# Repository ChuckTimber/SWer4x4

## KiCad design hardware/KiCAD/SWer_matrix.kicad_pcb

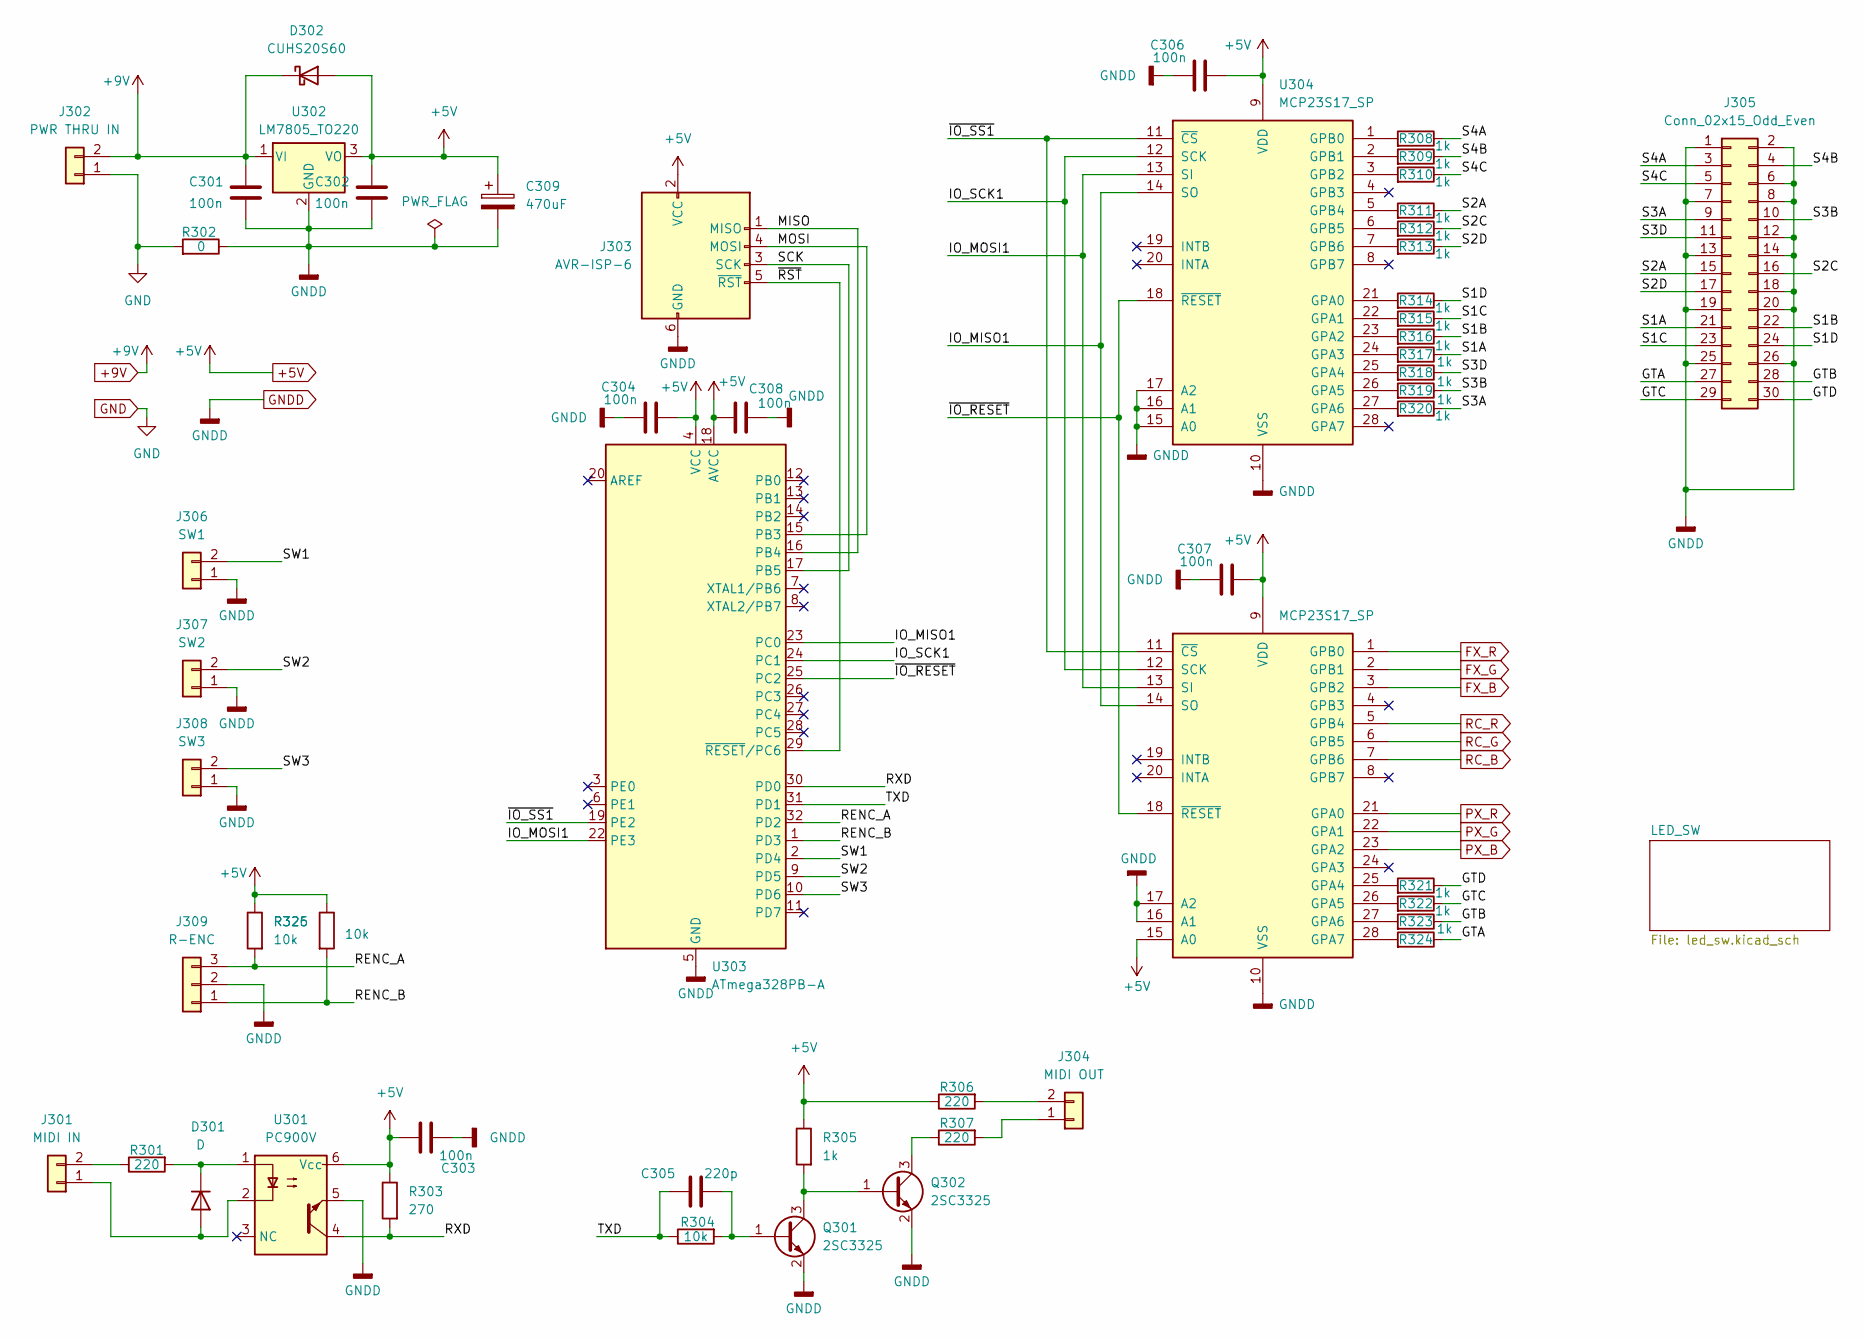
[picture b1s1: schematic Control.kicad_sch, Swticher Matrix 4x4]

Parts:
C301, C302, C303, C304, C306, C307, C308: 100n; C_0603_1608Metric_Pad1.08x0.95mm_HandSolder
C305: 220p; C_Disc_D6.0mm_W2.5mm_P5.00mm
C309: 470uF; CP_Radial_D12.5mm_P5.00mm
D301: D; Nexperia_CFP3_SOD-123W
D302: CUHS20S60; D_1210_3225Metric_Pad1.42x2.65mm_HandSolder
J301: MIDI IN; PinSocket_1x02_P2.54mm_Vertical
J302: PWR THRU IN; PinSocket_1x02_P2.54mm_Vertical
J303: AVR-ISP-6; PinHeader_2x03_P2.54mm_Vertical
J304: MIDI OUT; PinSocket_1x02_P2.54mm_Vertical
J305: Conn_02x15_Odd_Even; PinHeader_2x15_P2.54mm_Vertical
J306: SW1; PinSocket_1x02_P2.54mm_Vertical
J307: SW2; PinSocket_1x02_P2.54mm_Vertical
J308: SW3; PinSocket_1x02_P2.54mm_Vertical
J309: R-ENC; PinHeader_1x03_P2.54mm_Vertical
Q301, Q302: 2SC3325; SOT-323_SC-70
R301, R306, R307: 220; R_0603_1608Metric_Pad0.98x0.95mm_HandSolder
R302: 0; R_0603_1608Metric_Pad0.98x0.95mm_HandSolder
R303: 270; R_Axial_DIN0204_L3.6mm_D1.6mm_P2.54mm_Vertical
R304, R325, R326: 10k; R_0603_1608Metric_Pad0.98x0.95mm_HandSolder
R305, R308, R309, R310, R311, R312, R313, R314, R315, R316, R317, R318, R319, R320, R321, R322, R323, R324: 1k; R_0603_1608Metric_Pad0.98x0.95mm_HandSolder
U301: PC900V; DIP-6_W7.62mm
U302: LM7805_TO220; TO-220-3_Vertical
U303: ATmega328PB-A; TQFP-32_7x7mm_P0.8mm
U304, U305: MCP23S17_SP; DIP-28_W7.62mm

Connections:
+5V: C302.1, C303.2, C304.2, C306.2, C307.2, C308.2, C309.1, D302.2 (A), J303.2 (VCC), R303.1, R305.1, R306.1, R325.1, R326.1, U301.6 (Vcc), U302.3 (VO), U303.4 (VCC), U303.18 (AVCC), U304.9 (VDD), U305.9 (VDD), U305.15 (A0); also elsewhere on the board
+9V: C301.1, D302.1 (K), J302.2, U302.1 (VI); also elsewhere on the board
/Control/GTA: J305.27, R324.1
/Control/GTB: J305.28, R323.1
/Control/GTC: J305.29, R322.1
/Control/GTD: J305.30, R321.1
/Control/IO_MISO1: U303.23 (PC0), U304.14 (SO), U305.14 (SO)
/Control/IO_MOSI1: U303.22 (PE3), U304.13 (SI), U305.13 (SI)
/Control/IO_SCK1: U303.24 (PC1), U304.12 (SCK), U305.12 (SCK)
/Control/MISO: J303.1 (MISO), U303.16 (PB4)
/Control/MOSI: J303.4 (MOSI), U303.15 (PB3)
/Control/RENC_A: J309.3, R325.2, U303.32 (PD2)
/Control/RENC_B: J309.1, R326.2, U303.1 (PD3)
/Control/RXD: R303.2, U301.4, U303.30 (PD0)
/Control/S1A: J305.21, R317.1
/Control/S1B: J305.22, R316.1
/Control/S1C: J305.23, R315.1
/Control/S1D: J305.24, R314.1
/Control/S2A: J305.15, R311.1
/Control/S2C: J305.16, R312.1
/Control/S2D: J305.17, R313.1
/Control/S3A: J305.9, R320.1
/Control/S3B: J305.10, R319.1
/Control/S3D: J305.11, R318.1
/Control/S4A: J305.3, R308.1
/Control/S4B: J305.4, R309.1
/Control/S4C: J305.5, R310.1
/Control/SCK: J303.3 (SCK), U303.17 (PB5)
/Control/SW1: J306.2, U303.2 (PD4)
/Control/SW2: J307.2, U303.9 (PD5)
/Control/SW3: J308.2, U303.10 (PD6)
/Control/TXD: C305.1, R304.1, U303.31 (PD1)
/Control/~IO_RESET: U303.25 (PC2), U304.18 (~RESET), U305.18 (~RESET)
/Control/~IO_SS1: U303.19 (PE2), U304.11 (~CS), U305.11 (~CS)
/Control/~RST: J303.5 (~RST), U303.29 (~RESET/PC6)
FX_B: U305.3 (GPB2); also elsewhere on the board
FX_G: U305.2 (GPB1); also elsewhere on the board
FX_R: U305.1 (GPB0); also elsewhere on the board
GND: J302.1, R302.2; also elsewhere on the board
GNDD: C301.2, C302.2, C303.1, C304.1, C306.1, C307.1, C308.1, C309.2, J303.6 (GND), J305.1, J305.2, J305.6, J305.7, J305.8, J305.12, J305.13, J305.14, J305.18, J305.19, J305.20, J305.25, J305.26, J306.1, J307.1, J308.1, J309.2, Q301.2 (E), Q302.2 (E), R302.1, U301.5, U302.2 (GND), U303.5 (GND), U303.21 (GND), U304.10 (VSS), U304.15 (A0), U304.16 (A1), U304.17 (A2), U305.10 (VSS), U305.16 (A1), U305.17 (A2); also elsewhere on the board
unnamed: D301.2 (A), J301.1, U301.2
unnamed: D301.1 (K), R301.2, U301.1
unnamed: J301.2, R301.1
unnamed: J304.1, R307.2
unnamed: J304.2, R306.2
unnamed: C305.2, Q301.1 (B), R304.2
unnamed: Q301.3 (C), Q302.1 (B), R305.2
unnamed: Q302.3 (C), R307.1
unnamed: R314.2, U304.21 (GPA0)
unnamed: R315.2, U304.22 (GPA1)
unnamed: R316.2, U304.23 (GPA2)
unnamed: R317.2, U304.24 (GPA3)
unnamed: R318.2, U304.25 (GPA4)
unnamed: R319.2, U304.26 (GPA5)
unnamed: R320.2, U304.27 (GPA6)
unnamed: R308.2, U304.1 (GPB0)
unnamed: R309.2, U304.2 (GPB1)
unnamed: R310.2, U304.3 (GPB2)
unnamed: R311.2, U304.5 (GPB4)
unnamed: R312.2, U304.6 (GPB5)
unnamed: R313.2, U304.7 (GPB6)
unnamed: R321.2, U305.25 (GPA4)
unnamed: R322.2, U305.26 (GPA5)
unnamed: R323.2, U305.27 (GPA6)
unnamed: R324.2, U305.28 (GPA7)
PX_B: U305.23 (GPA2); also elsewhere on the board
PX_G: U305.22 (GPA1); also elsewhere on the board
PX_R: U305.21 (GPA0); also elsewhere on the board
RC_B: U305.7 (GPB6); also elsewhere on the board
RC_G: U305.6 (GPB5); also elsewhere on the board
RC_R: U305.5 (GPB4); also elsewhere on the board

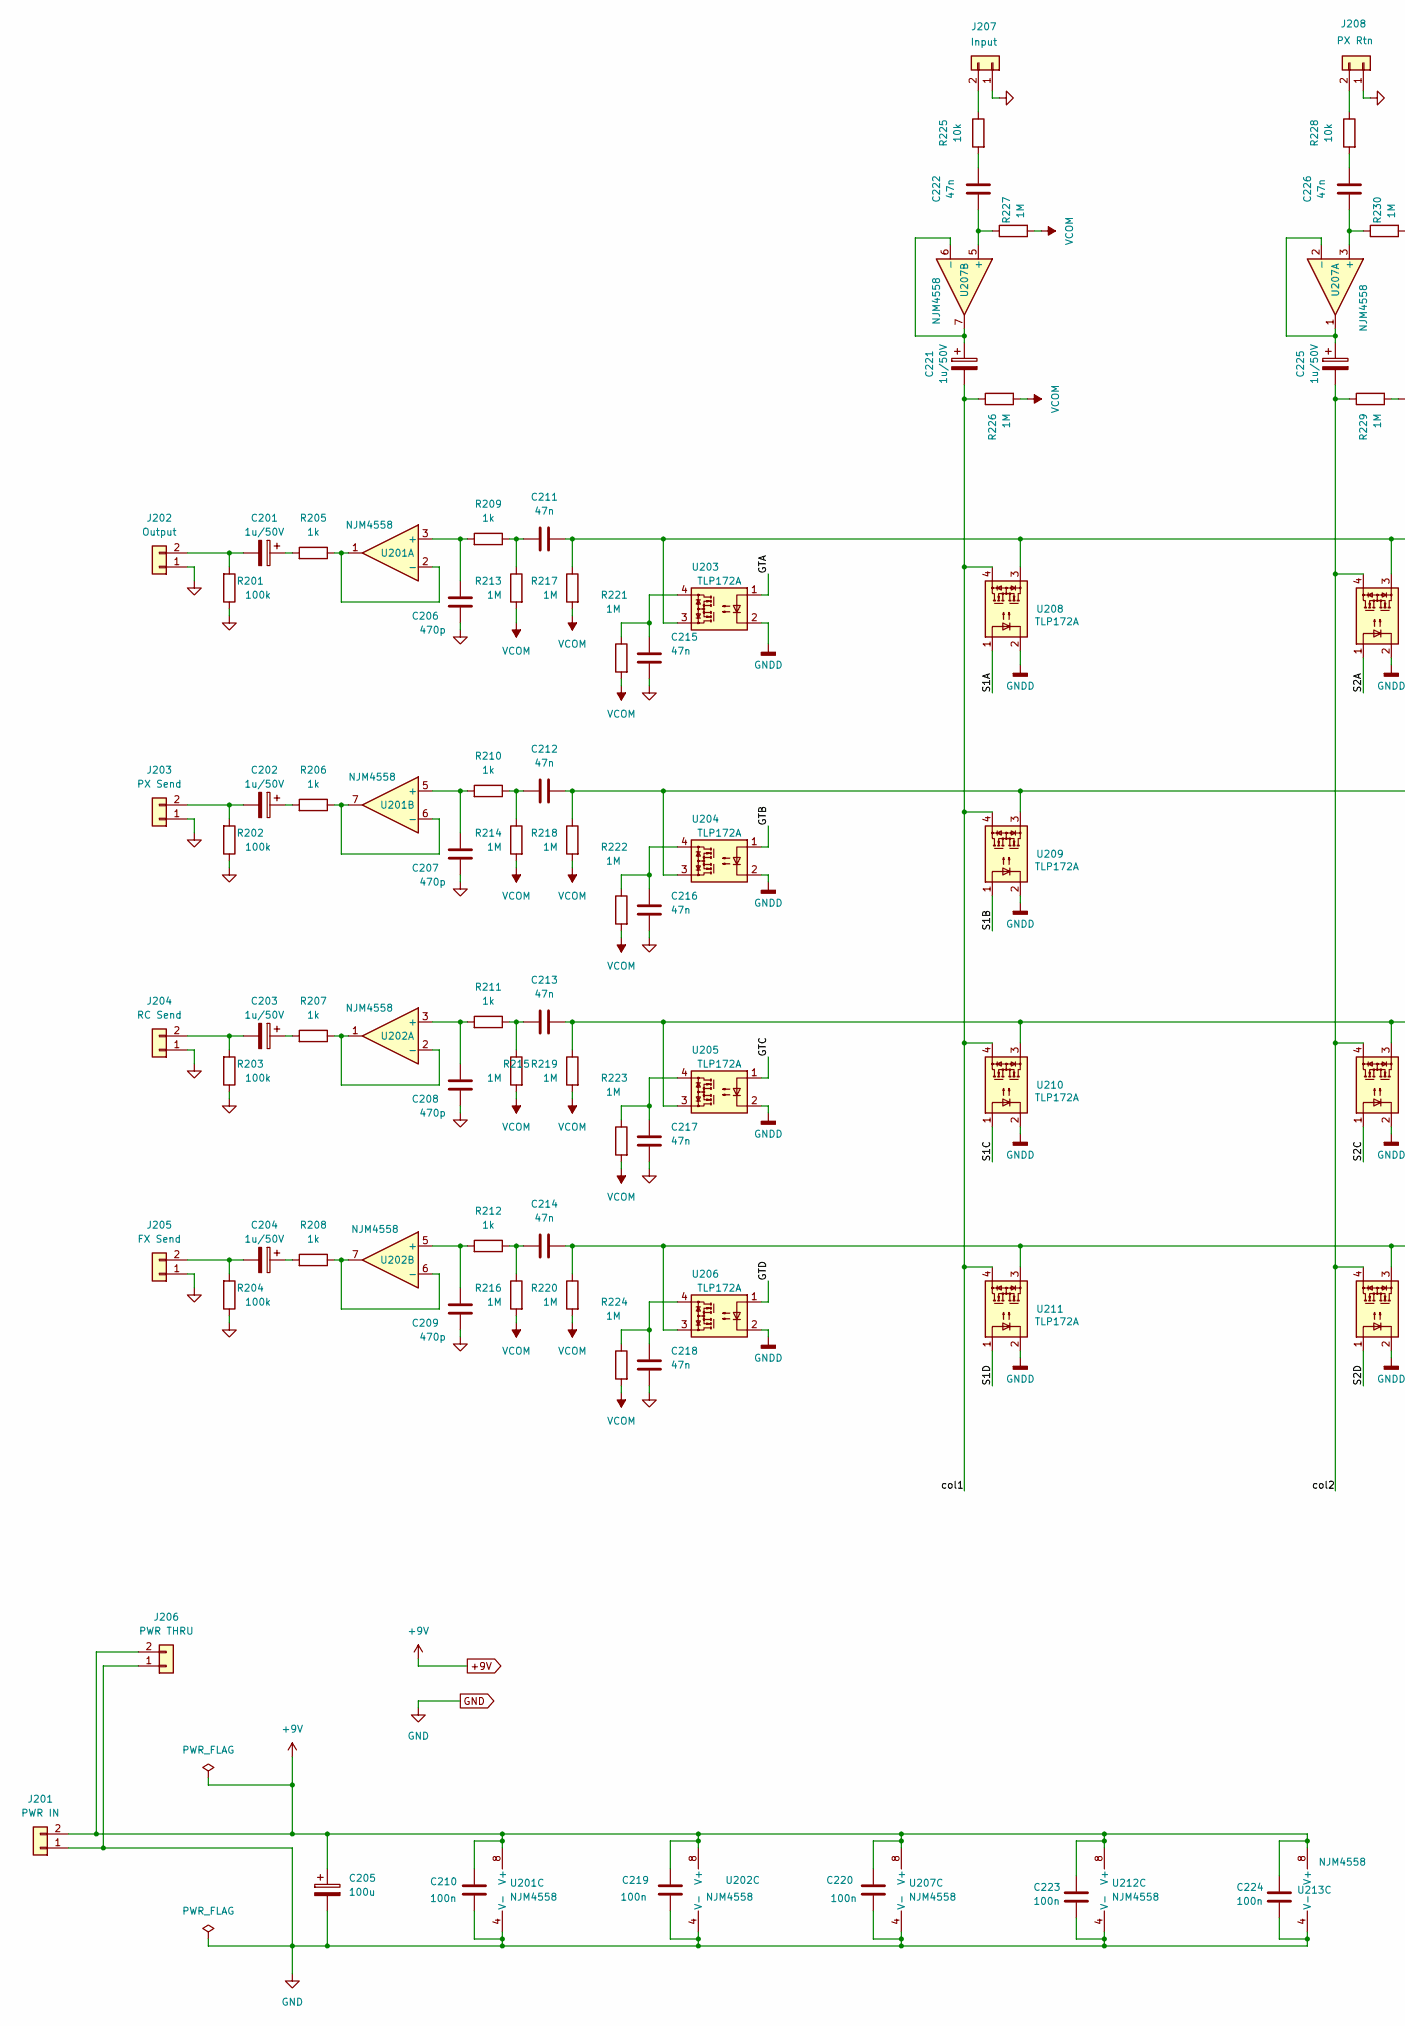
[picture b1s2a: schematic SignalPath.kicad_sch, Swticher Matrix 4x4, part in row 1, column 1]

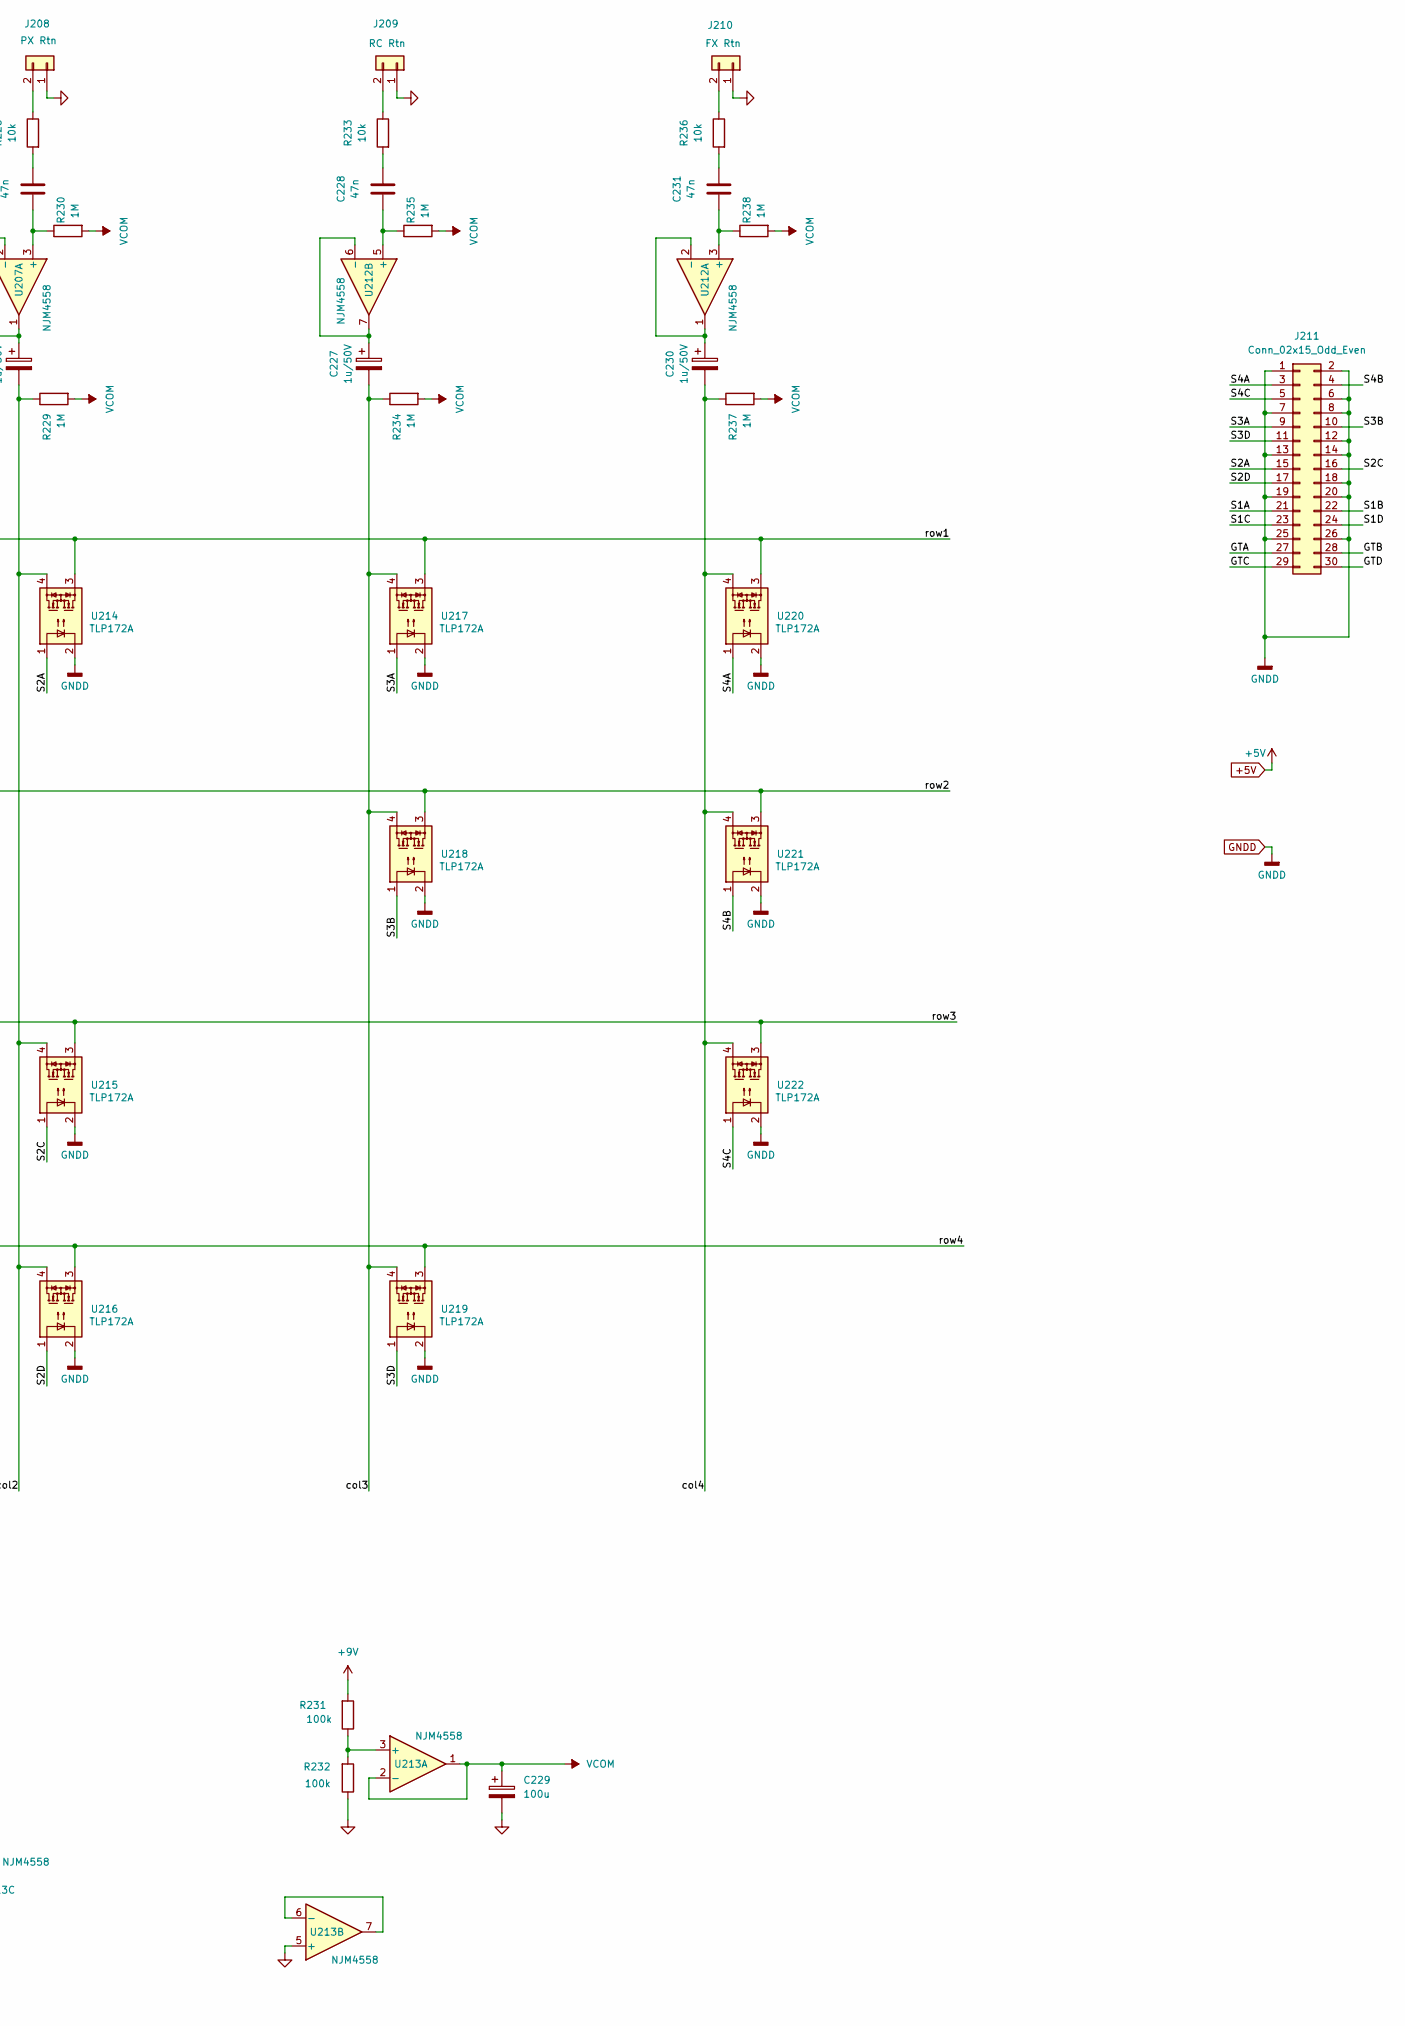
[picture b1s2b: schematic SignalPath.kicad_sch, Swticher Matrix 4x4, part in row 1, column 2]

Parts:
C201, C202, C203, C204, C221, C225, C227, C230: 1u/50V; CP_Radial_D5.0mm_P2.00mm
C205, C229: 100u; CP_Radial_D5.0mm_P2.00mm
C206, C207, C208, C209: 470p; C_Disc_D6.0mm_W2.5mm_P5.00mm
C210, C219, C220, C223, C224: 100n; C_0603_1608Metric_Pad1.08x0.95mm_HandSolder
C211, C212, C213, C214, C215, C216, C217, C218, C222, C226, C228, C231: 47n; C_Rect_L7.0mm_W2.0mm_P5.00mm
J201: PWR IN; PinSocket_1x02_P2.54mm_Vertical
J202: Output; PinSocket_1x02_P2.54mm_Vertical
J203: PX Send; PinSocket_1x02_P2.54mm_Vertical
J204: RC Send; PinSocket_1x02_P2.54mm_Vertical
J205: FX Send; PinSocket_1x02_P2.54mm_Vertical
J206: PWR THRU; PinSocket_1x02_P2.54mm_Vertical
J207: Input; PinSocket_1x02_P2.54mm_Vertical
J208: PX Rtn; PinSocket_1x02_P2.54mm_Vertical
J209: RC Rtn; PinSocket_1x02_P2.54mm_Vertical
J210: FX Rtn; PinSocket_1x02_P2.54mm_Vertical
J211: Conn_02x15_Odd_Even; PinHeader_2x15_P2.54mm_Vertical
R201, R202, R203, R204, R231, R232: 100k; R_0603_1608Metric_Pad0.98x0.95mm_HandSolder
R205, R206, R207, R208, R209, R210, R211, R212: 1k; R_0603_1608Metric_Pad0.98x0.95mm_HandSolder
R213, R214, R215, R216, R217, R218, R219, R220, R221, R222, R223, R224, R226, R227, R229, R230, R234, R235, R237, R238: 1M; R_0603_1608Metric_Pad0.98x0.95mm_HandSolder
R225, R228, R233, R236: 10k; R_0603_1608Metric_Pad0.98x0.95mm_HandSolder
U201, U202, U207, U212, U213: NJM4558; DMP-8_P1.27mm_HandSolder
U203, U204, U205, U206, U208, U209, U210, U211, U214, U215, U216, U217, U218, U219, U220, U221, U222: TLP172A; SOP-4_3.8x4.1mm_P2.54mm

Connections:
+9V: C205.1, C210.1, C219.1, C220.1, C223.1, C224.1, J201.2, J206.2, R231.2, U201.8 (V+), U202.8 (V+), U207.8 (V+), U212.8 (V+), U213.8 (V+); also elsewhere on the board
/SignalPath/GTA: J211.27, U203.1
/SignalPath/GTB: J211.28, U204.1
/SignalPath/GTC: J211.29, U205.1
/SignalPath/GTD: J211.30, U206.1
/SignalPath/S1A: J211.21, U208.1
/SignalPath/S1B: J211.22, U209.1
/SignalPath/S1C: J211.23, U210.1
/SignalPath/S1D: J211.24, U211.1
/SignalPath/S2A: J211.15, U214.1
/SignalPath/S2C: J211.16, U215.1
/SignalPath/S2D: J211.17, U216.1
/SignalPath/S3A: J211.9, U217.1
/SignalPath/S3B: J211.10, U218.1
/SignalPath/S3D: J211.11, U219.1
/SignalPath/S4A: J211.3, U220.1
/SignalPath/S4B: J211.4, U221.1
/SignalPath/S4C: J211.5, U222.1
/SignalPath/col1: C221.2, R226.1, U208.4, U209.4, U210.4, U211.4
/SignalPath/col2: C225.2, R229.1, U214.4, U215.4, U216.4
/SignalPath/col3: C227.2, R234.1, U217.4, U218.4, U219.4
/SignalPath/col4: C230.2, R237.1, U220.4, U221.4, U222.4
/SignalPath/row1: C211.1, R217.1, U203.3, U208.3, U214.3, U217.3, U220.3
/SignalPath/row2: C212.2, R218.1, U204.3, U209.3, U218.3, U221.3
/SignalPath/row3: C213.1, R219.1, U205.3, U210.3, U215.3, U222.3
/SignalPath/row4: C214.1, R220.1, U206.3, U211.3, U216.3, U219.3
GND: C205.2, C206.2, C207.2, C208.2, C209.2, C210.2, C215.2, C216.2, C217.2, C218.2, C219.2, C220.2, C223.2, C224.2, C229.2, J201.1, J202.1, J203.1, J204.1, J205.1, J206.1, J207.1, J208.1, J209.1, J210.1, R201.1, R202.1, R203.1, R204.1, R232.1, U201.4 (V-), U202.4 (V-), U207.4 (V-), U212.4 (V-), U213.4 (V-), U213.5 (+); also elsewhere on the board
GNDD: J211.1, J211.2, J211.6, J211.7, J211.8, J211.12, J211.13, J211.14, J211.18, J211.19, J211.20, J211.25, J211.26, U203.2, U204.2, U205.2, U206.2, U208.2, U209.2, U210.2, U211.2, U214.2, U215.2, U216.2, U217.2, U218.2, U219.2, U220.2, U221.2, U222.2; also elsewhere on the board
unnamed: C201.1, R205.2
unnamed: C202.1, R206.2
unnamed: C203.1, R207.2
unnamed: C204.1, R208.2
unnamed: C211.2, R209.1, R213.1
unnamed: C212.1, R210.1, R214.1
unnamed: C213.2, R211.1, R215.1
unnamed: C214.2, R212.1, R216.1
unnamed: C215.1, R221.1, U203.4
unnamed: C216.1, R222.1, U204.4
unnamed: C217.1, R223.1, U205.4
unnamed: C218.1, R224.1, U206.4
unnamed: C222.1, R225.2
unnamed: C226.1, R228.2
unnamed: C228.1, R233.2
unnamed: C231.1, R236.2
unnamed: C201.2, J202.2, R201.2
unnamed: C202.2, J203.2, R202.2
unnamed: C203.2, J204.2, R203.2
unnamed: C204.2, J205.2, R204.2
unnamed: J207.2, R225.1
unnamed: J208.2, R228.1
unnamed: J209.2, R233.1
unnamed: J210.2, R236.1
unnamed: C206.1, R209.2, U201.3 (+)
unnamed: R205.1, U201.1, U201.2 (-)
unnamed: C207.1, R210.2, U201.5 (+)
unnamed: R206.1, U201.6 (-), U201.7
unnamed: C208.1, R211.2, U202.3 (+)
unnamed: R207.1, U202.1, U202.2 (-)
unnamed: C209.1, R212.2, U202.5 (+)
unnamed: R208.1, U202.6 (-), U202.7
unnamed: C226.2, R230.1, U207.3 (+)
unnamed: C225.1, U207.1, U207.2 (-)
unnamed: C222.2, R227.1, U207.5 (+)
unnamed: C221.1, U207.6 (-), U207.7
unnamed: C231.2, R238.1, U212.3 (+)
unnamed: C230.1, U212.1, U212.2 (-)
unnamed: C228.2, R235.1, U212.5 (+)
unnamed: C227.1, U212.6 (-), U212.7
unnamed: R231.1, R232.2, U213.3 (+)
unnamed: U213.6 (-), U213.7
VCOM: C229.1, R213.2, R214.2, R215.2, R216.2, R217.2, R218.2, R219.2, R220.2, R221.2, R222.2, R223.2, R224.2, R226.2, R227.2, R229.2, R230.2, R234.2, R235.2, R237.2, R238.2, U213.1, U213.2 (-)

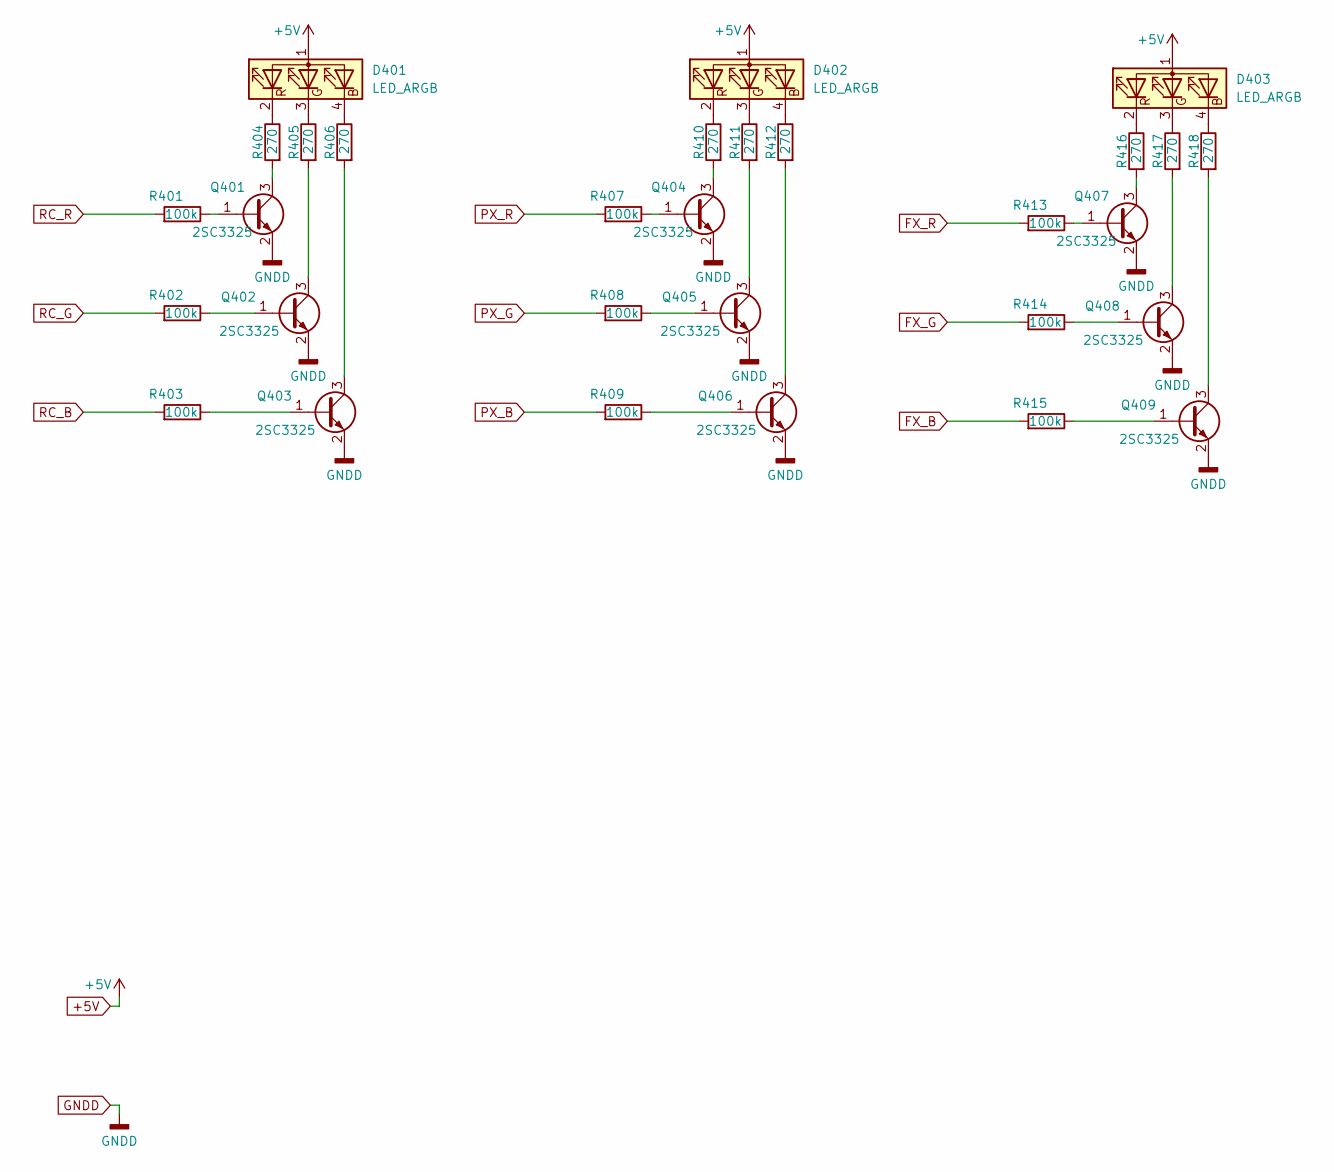
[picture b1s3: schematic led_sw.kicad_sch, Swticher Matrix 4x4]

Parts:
D401, D402, D403: LED_ARGB; PinHeader_1x04_P2.54mm_Vertical
Q401, Q402, Q403, Q404, Q405, Q406, Q407, Q408, Q409: 2SC3325; SOT-323_SC-70
R401, R402, R403, R407, R408, R409, R413, R414, R415: 100k; R_0603_1608Metric_Pad0.98x0.95mm_HandSolder
R404, R405, R406, R410, R411, R412, R416, R417, R418: 270; R_Axial_DIN0204_L3.6mm_D1.6mm_P2.54mm_Vertical

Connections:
+5V: D401.1 (A), D402.1 (A), D403.1 (A); also elsewhere on the board
FX_B: R415.2; also elsewhere on the board
FX_G: R414.2; also elsewhere on the board
FX_R: R413.2; also elsewhere on the board
GNDD: Q401.2 (E), Q402.2 (E), Q403.2 (E), Q404.2 (E), Q405.2 (E), Q406.2 (E), Q407.2 (E), Q408.2 (E), Q409.2 (E); also elsewhere on the board
unnamed: D401.4 (BK), R406.1
unnamed: D401.3 (GK), R405.1
unnamed: D401.2 (RK), R404.1
unnamed: D402.4 (BK), R412.1
unnamed: D402.3 (GK), R411.1
unnamed: D402.2 (RK), R410.1
unnamed: D403.4 (BK), R418.1
unnamed: D403.3 (GK), R417.1
unnamed: D403.2 (RK), R416.1
unnamed: Q401.1 (B), R401.1
unnamed: Q401.3 (C), R404.2
unnamed: Q402.1 (B), R402.1
unnamed: Q402.3 (C), R405.2
unnamed: Q403.1 (B), R403.1
unnamed: Q403.3 (C), R406.2
unnamed: Q404.1 (B), R407.1
unnamed: Q404.3 (C), R410.2
unnamed: Q405.1 (B), R408.1
unnamed: Q405.3 (C), R411.2
unnamed: Q406.1 (B), R409.1
unnamed: Q406.3 (C), R412.2
unnamed: Q407.1 (B), R413.1
unnamed: Q407.3 (C), R416.2
unnamed: Q408.1 (B), R414.1
unnamed: Q408.3 (C), R417.2
unnamed: Q409.1 (B), R415.1
unnamed: Q409.3 (C), R418.2
PX_B: R409.2; also elsewhere on the board
PX_G: R408.2; also elsewhere on the board
PX_R: R407.2; also elsewhere on the board
RC_B: R403.2; also elsewhere on the board
RC_G: R402.2; also elsewhere on the board
RC_R: R401.2; also elsewhere on the board

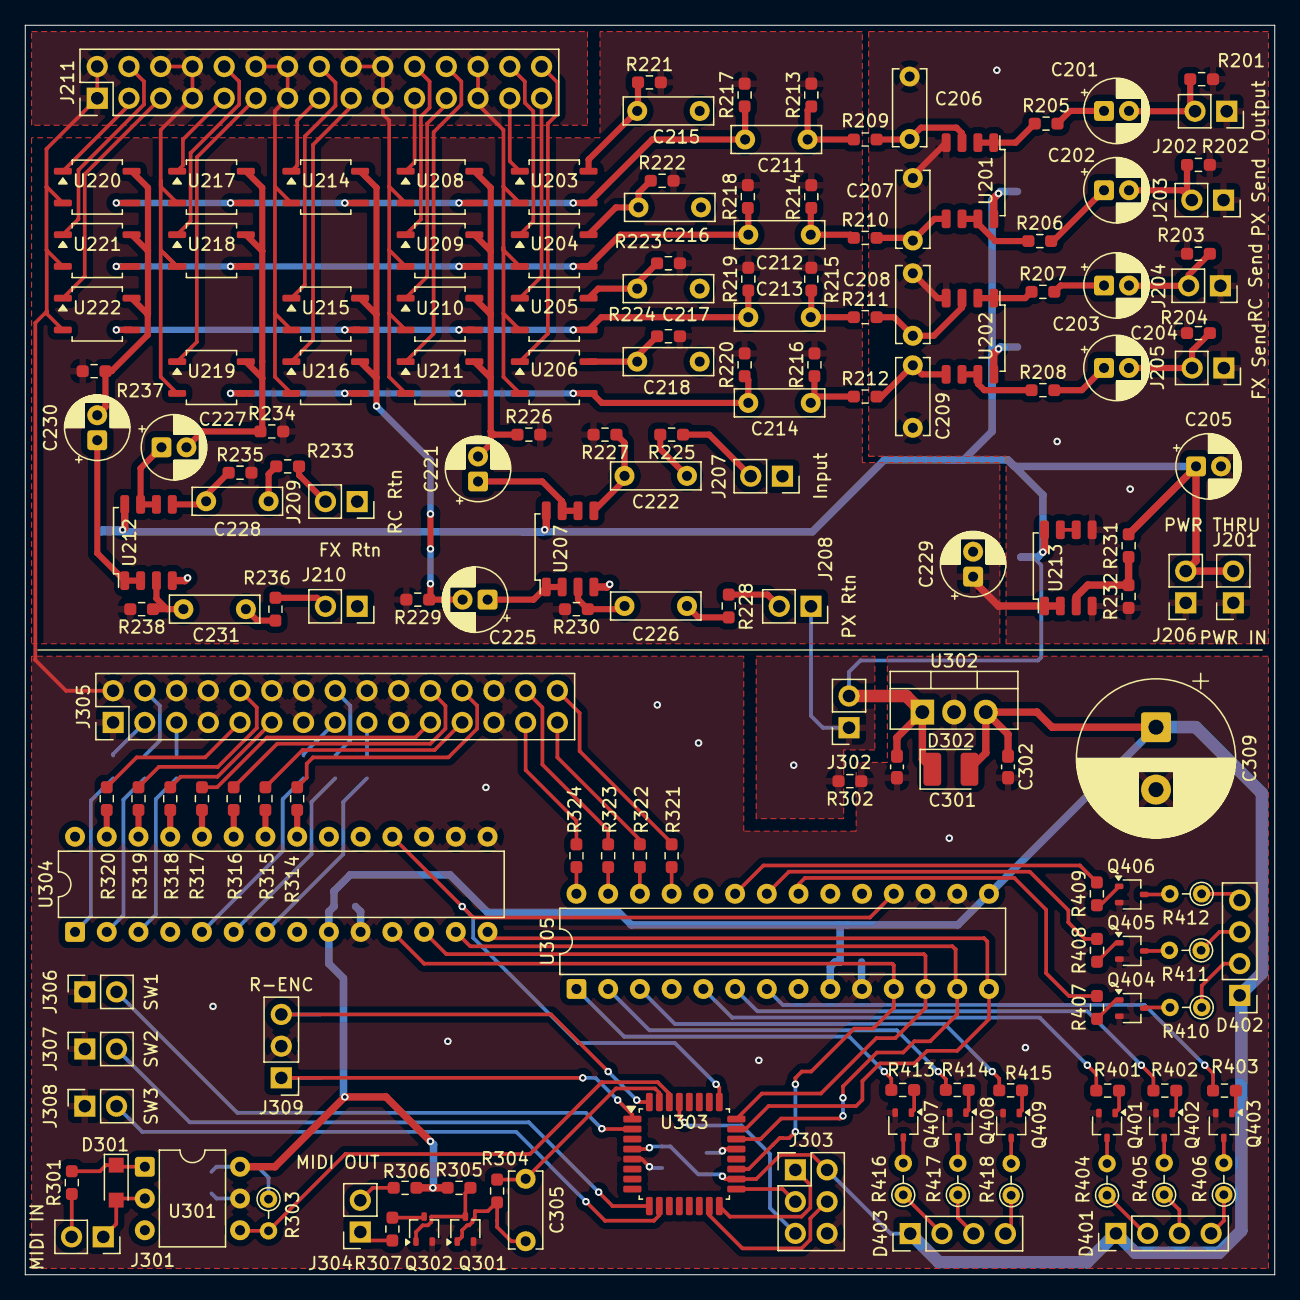
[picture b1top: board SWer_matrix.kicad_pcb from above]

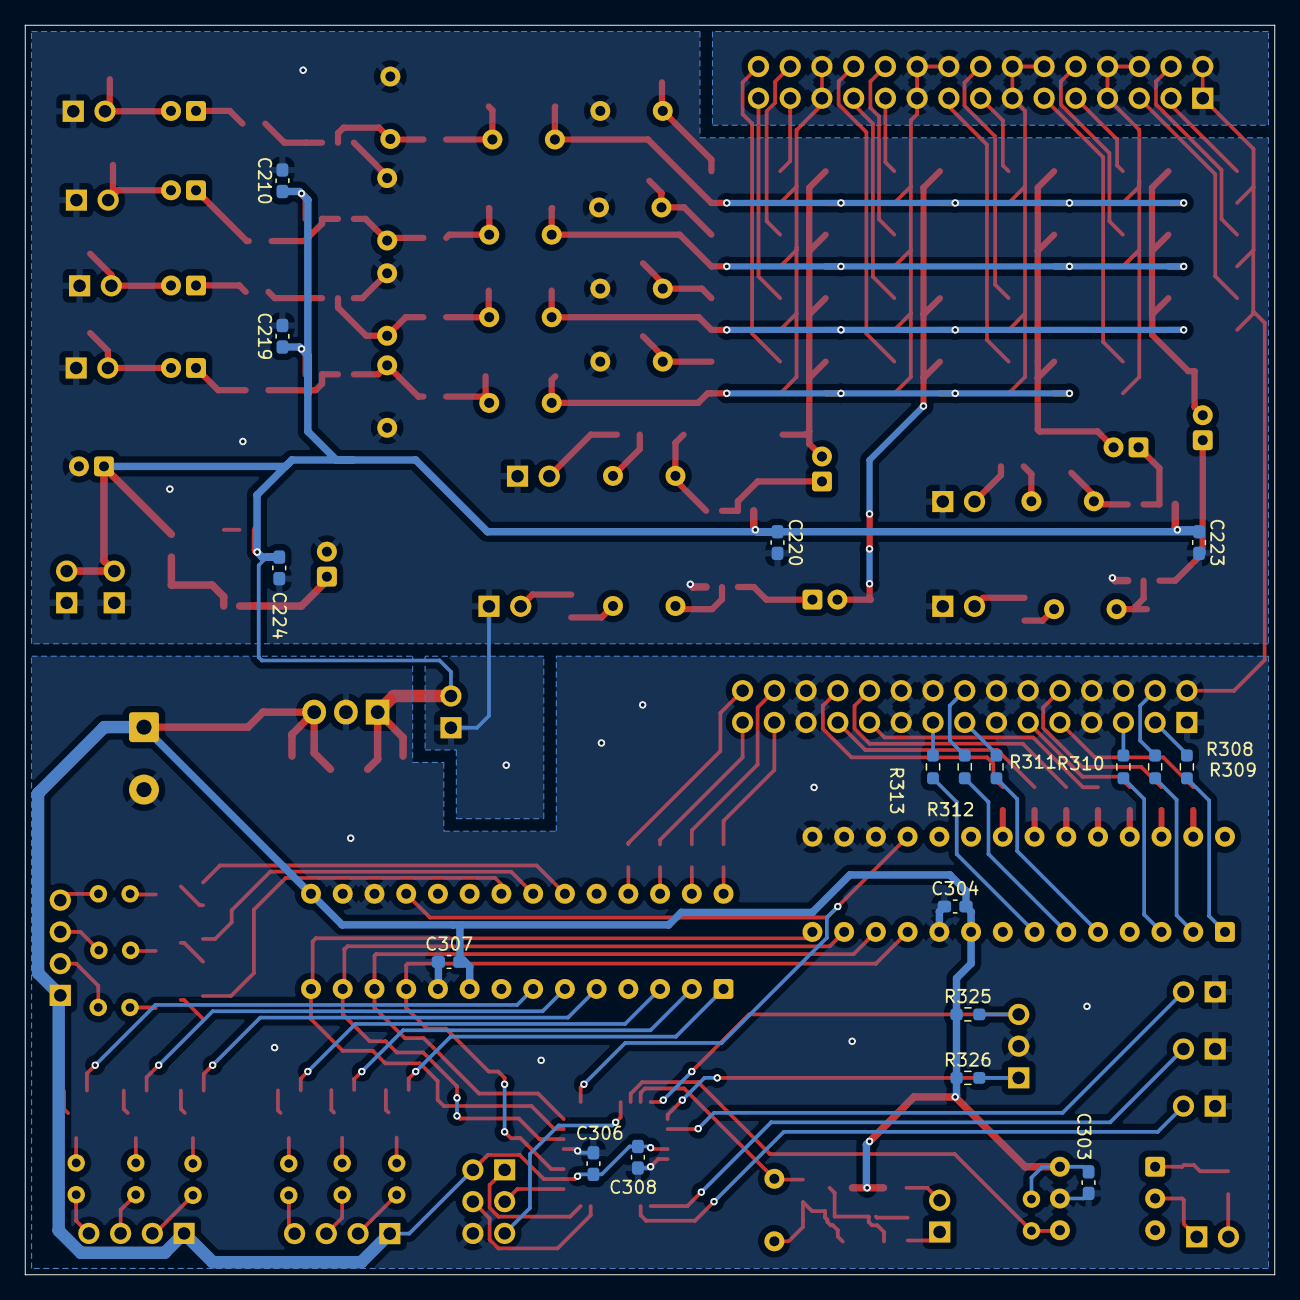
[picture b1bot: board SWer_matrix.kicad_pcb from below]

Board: 2 copper layers, 100.0 x 100.0 mm, 185 parts (18 on the bottom side), 166 nets.

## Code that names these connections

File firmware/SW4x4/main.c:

/*
 * SW4x4 main.c
 *
 * Created: 2026/01/09 14:40:51
 * Author : Chuck
 */ 

#include "config.h"

#include <inttypes.h>
#include <stdbool.h>
#include <avr/io.h>
#include <avr/sleep.h>

#include "timer.h"
#include "spi.h"
#include "ui.h"
#include "renc.h"



typedef enum { 
	COL_0 = 0, 
	COL_R, 
	COL_G, 
	COL_Y, 
	COL_B, 
	COL_M, 
	COL_C, 
	COL_W
} LedColor_t;

/*
Dev0 16bit { GPA[7:0], GPB[7:0] } = 
	{  nc,  S3A, S3B, S3D, S1A, S1B, S1C, S1D, 
	   nc,  S2D, S2C, S2A, nc,  S4C, S4B, S4A  }

Dev1 16bit { GPA[7:0], GPB[7:0] } = 
	{  GTA, GTB, GTC, GTD, nc,  P_B, P_G, P_R, 
	   nc,  R_B, R_G, R_R, nc,  F_B, F_G, F_R  }
*/

typedef enum {
	GTA = 31, 
	GTB = 30,
	GTC = 29,
	GTD = 28,
	nc0 = 27,
	P_B = 26,
	P_G = 25,
	P_R = 24,	// LED slot1
	nc1 = 23,
	R_B = 22,
	R_G = 21,
	R_R = 20,	// LED slot2
	nc2 = 19,
	F_B = 18,
	F_G = 17,
	F_R = 16,	// LED slot3
	nc3 = 15,
	S3A = 14,
	S3B = 13,
	S3D = 12,
	S1A = 11,
	S1B = 10,
	S1C = 9,
	S1D = 8,
	nc4 = 7,
	S2D = 6,
	S2C = 5,
	S2A = 4,
	nc5 = 3,
	S4C = 2,
	S4B = 1,
	S4A = 0,
	LED1 = 24,	// LED slot1
	LED2 = 20,	// LED slot2
	LED3 = 16,	// LED slot3
} BitPos;

#define LED(d, p)	((long)d << p)

#define BIT(pos) (1UL << (pos))

const uint32_t EMPTY = BIT(nc0)|BIT(nc1)|BIT(nc2)|BIT(nc3)|BIT(nc4);
const uint32_t _0AWO = BIT(S1A) | BIT(GTA);
const uint32_t _1AWO = BIT(S2A) | BIT(GTA);
const uint32_t _2AWO = BIT(S3A) | BIT(GTA);
const uint32_t _3AWO = BIT(S4A) | BIT(GTA);
const uint32_t _0BX1 = BIT(S1B) | BIT(GTB);
const uint32_t _2BX1 = BIT(S3B) | BIT(GTB);
const uint32_t _3BX1 = BIT(S4B) | BIT(GTB);
const uint32_t _0CY2 = BIT(S1C) | BIT(GTC);
const uint32_t _1CY2 = BIT(S2C) | BIT(GTC);
const uint32_t _3CY2 = BIT(S4C) | BIT(GTC);
const uint32_t _0DZ3 = BIT(S1D) | BIT(GTD);
const uint32_t _1DZ3 = BIT(S2D) | BIT(GTD);
const uint32_t _2DZ3 = BIT(S3D) | BIT(GTD);

#define BYPASS (_0AWO| LED(COL_G, LED1) | LED(COL_G, LED2) | LED(COL_G, LED3))
#define XLIMIT 6
#define YLIMIT 3

void timer_service(void)
{
	uint8_t tmcnt = getTM0Cnt();
	
	if( tmcnt & 0x01 )
		keyScan();
	else
		reScan();

}

int clamp (int v, int min, int max)
{
	if (v < min) return min;
	if (v > max) return max;
	return v;
}

int main(void)
{

	//static uint16_t	c = 0;
	unsigned char i, j;

	keyInit();
	reInit();
	reEnable();
	initSPI();
	timer0Init();
	

	static uint32_t command_table[XLIMIT+1][YLIMIT+1];
	
	for (i = 0; i < XLIMIT+1; i++ )
		for (j = 0; j < YLIMIT+1; j++)
			command_table[i][j] = EMPTY;
			
	command_table[0][0] = _0AWO                         | LED(COL_G, LED1) | LED(COL_G, LED2) | LED(COL_G, LED3) ;
	command_table[1][0] = _0BX1 | _1CY2 | _2DZ3 | _3AWO | LED(COL_W, LED1) | LED(COL_R, LED2) | LED(COL_G, LED3) ;
	command_table[2][0] = _0BX1 | _1DZ3 | _3CY2 | _2AWO | LED(COL_W, LED1) | LED(COL_G, LED2) | LED(COL_R, LED3) ;
	command_table[3][0] = _0CY2 | _2BX1 | _1DZ3 | _3AWO | LED(COL_R, LED1) | LED(COL_W, LED2) | LED(COL_G, LED3) ;
	command_table[4][0] = _0CY2 | _2DZ3 | _3BX1 | _1AWO | LED(COL_R, LED1) | LED(COL_G, LED2) | LED(COL_W, LED3) ;
	command_table[5][0] = _0DZ3 | _3BX1 | _1CY2 | _2AWO | LED(COL_G, LED1) | LED(COL_W, LED2) | LED(COL_R, LED3) ;
	command_table[6][0] = _0DZ3 | _3CY2 | _2BX1 | _1AWO | LED(COL_G, LED1) | LED(COL_R, LED2) | LED(COL_W, LED3) ;
	command_table[1][1] = _0BX1 | _1CY2 | _2AWO         | LED(COL_W, LED1) | LED(COL_R, LED2) ;
	command_table[2][1] = _0BX1 | _1DZ3 | _3AWO ;
	command_table[3][1] = _0CY2 | _2BX1 | _1AWO ;
	command_table[4][1] = _0CY2 | _2DZ3 | _3AWO ;
	command_table[5][1] = _0DZ3 | _3BX1 | _1AWO ;
	command_table[6][1] = _0DZ3 | _3CY2 | _2AWO ;
	command_table[1][2] = _0BX1 | _1AWO ;
	command_table[2][2] = _0BX1 | _1AWO ;
	command_table[3][2] = _0CY2 | _2AWO ;
	command_table[4][2] = _0CY2 | _2AWO ;
	command_table[5][2] = _0DZ3 | _3AWO ;
	command_table[6][2] = _0DZ3 | _3AWO ;
	command_table[1][3] = _0AWO ;
	command_table[2][3] = _0AWO ;
	command_table[3][3] = _0AWO ;
	command_table[4][3] = _0AWO ;
	command_table[5][3] = _0AWO ;
	command_table[6][3] = _0AWO ;

	typedef struct {
		unsigned char x;
		unsigned char y;
		uint32_t data;
	} Table;
	
	static Table current;

	current.x = 0;
	current.y = 0;
	current.data = BYPASS;


	re_event_t re;
	key_event_t key;

    /* Replace with your application code */
	/*
    while ( c < 0x7ff ) 
    {
		sndSPI8( Dev1, GPB, c & 0x0FF);
		sndSPI8( Dev1, GPA, c++ >> 8);
		for (i = 0; i < 2; ) {	// delay 96msec
			if (getTM0Flg()) {
				i++;
			}
		}
    }
	*/
	sndSPI8( Dev0, GPA, 0x00);
	sndSPI8( Dev0, GPB, 0x00);
	sndSPI8( Dev1, GPA, 0x00);
	sndSPI8( Dev1, GPB, 0x00);

	for (j = 0; j < XLIMIT + 1; j++) {
		sndSPI32( command_table[j][0] );
		for (i = 0; i < 250; ) {	// delay 96msec
			if (getTM0Flg()) {
				i++;
			}
		}

	}


	while (1) {
		sleep_mode();
		timer_service();
		
		if (reGetEvent(&re)) {
			if ( re.rotation == cRE_RightTurn ) {
				current.x = clamp( current.x + 1, 0, XLIMIT );
				current.data = command_table[current.x][current.y];
			} else if ( re.rotation == cRE_LeftTurn ) {
				current.x = clamp( current.x - 1, 0, XLIMIT );
				current.data = command_table[current.x][current.y];
			}
			sndSPI32( current.data );
		}
		if (keyGetEvent(&key)) {
			
		}
	}
}

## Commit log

2026-01-19 File addition.
2026-01-19 Added a FreeCAD file.
2026-01-19 Added a picture and refined readme.
2026-01-19 Modified picture rendering.
2026-01-19 Create LICENSE.md
    Added LICENSE.md
